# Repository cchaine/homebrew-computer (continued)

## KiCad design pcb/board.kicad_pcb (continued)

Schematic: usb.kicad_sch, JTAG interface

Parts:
C28, C29, C30, C33, C37, C39, C40, C41, C42, C43, C44, C45, C46, C48: 0.1u; C_0402_1005Metric
C31: 10n; C_0402_1005Metric
C32, C36, C38: 4.7u; CP_Elec_4x4.5
C34: 3.3uF; C_1210_3225Metric
C35: 100pF; C_0402_1005Metric
C49, C50: 16p; C_0402_1005Metric
D1, D2: D_TVS; DO-214AC
FB1, FB2, FB3: 600R/0.5A; L_0603_1608Metric
J1: Conn_02x03_Counter_Clockwise; IDC-Header_2x03_P2.54mm_Horizontal
J2: USB_B; BEL_SS-52300-001
R7, R8, R9, R10, R14, R15, R16: 10k; R_0402_1005Metric
R11: 22; R_0402_1005Metric
R12: 68; R_0402_1005Metric
R13: 1k; R_0402_1005Metric
R17: 2.2k; R_0402_1005Metric
R18: 12k/1%; R_0402_1005Metric
U6: 74LVC1G04; SOT-23-5
U7: SN74AVC4T245PW; TSSOP-16_4.4x5mm_P0.65mm
U8: FT2232HQ; QFN-64-1EP_9x9mm_P0.5mm_EP4.35x4.35mm
U9: 93LCxxBxxOT; SOT-23-6
Y1: 12MHz; Crystal_SMD_EuroQuartz_MT-4Pin_3.2x2.5mm

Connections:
/USB interface/D+: D2.2 (A2), J2.3 (D+), U8.8 (DP)
/USB interface/D-: D1.2 (A2), J2.2 (D-), U8.7 (DM)
/USB interface/VBUS: FB1.1, R7.1, U6.2
/USB interface/VPHY: C36.1, C37.1, FB2.1, U8.4 (VPHY)
/USB interface/VPLL: C38.1, C39.1, FB3.1, U8.9 (VPLL)
GND: C28.2, C29.2, C30.2, C31.2, C32.2, C33.2, C34.2, C35.2, C36.2, C37.2, C38.2, C39.2, C40.2, C41.2, C42.2, C43.2, C44.2, C45.2, C46.2, C48.2, C49.2, C50.2, D1.1 (A1), D2.1 (A1), J1.4, J2.4 (GND), R7.2, R18.2, U6.3 (GND), U7.8 (GND), U7.9 (GND), U8.1 (GND), U8.5 (GND), U8.10 (AGND), U8.11 (GND), U8.13 (TEST), U8.15 (GND), U8.25 (GND), U8.35 (GND), U8.47 (GND), U8.51 (GND), U8.65 (GND), U9.2 (GND), Y1.2, Y1.4; also elsewhere on the board
unnamed: C31.1, FB1.2, J2.1 (VBUS)
unnamed: C35.1, R12.2
unnamed: C49.1, U8.2 (OSCI), Y1.1
unnamed: C50.1, U8.3 (OSCO), Y1.3
unnamed: R9.2, R11.2, U7.11 (2B1)
unnamed: R13.1, U8.14 (~RESET)
unnamed: R14.2, R17.2, U9.1 (DO)
unnamed: R15.2, U8.62 (EECLK), U9.4 (CLK)
unnamed: R16.2, U8.63 (EECS), U9.5 (CS)
unnamed: R17.1, U8.61 (EEDATA), U9.3 (DI)
unnamed: R18.1, U8.6 (REF)
unnamed: U6.4, U7.14 (2~OE), U7.15 (1~OE)
unnamed: U7.4 (1A1), U8.16 (ADBUS0)
unnamed: U7.5 (1A2), U8.17 (ADBUS1)
unnamed: U7.6 (2A1), U8.18 (ADBUS2)
unnamed: U7.7 (2A2), U8.19 (ADBUS3)
SPI_PROGRAM#: U8.52 (BCBUS1); also elsewhere on the board
TCK: J1.2, R12.1, U7.13 (1B1); also elsewhere on the board
TDI: J1.3, R8.2, U7.12 (1B2); also elsewhere on the board
TDO: J1.6, R11.1; also elsewhere on the board
TMS: J1.5, R10.2, U7.10 (2B2); also elsewhere on the board
USB_SPI_CLK: U8.38 (BDBUS0); also elsewhere on the board
USB_SPI_CONFIG_CS: U8.41 (BDBUS3); also elsewhere on the board
USB_SPI_MISO: U8.40 (BDBUS2); also elsewhere on the board
USB_SPI_MOSI: U8.39 (BDBUS1); also elsewhere on the board
USB_SPI_ROM_CS: U8.43 (BDBUS4); also elsewhere on the board
VCCAUX: C28.1, C29.1, C30.1, C32.1, C33.1, C34.1, C40.1, C41.1, C42.1, C43.1, C44.1, C45.1, C46.1, C48.1, FB2.2, FB3.2, J1.1, R8.1, R9.1, R10.1, R13.2, R14.1, R15.1, R16.1, U6.5 (VCC), U7.1 (VCCA), U7.2 (1DIR), U7.3 (2DIR), U7.16 (VCCB), U8.12 (VCORE), U8.20 (VCCIO), U8.31 (VCCIO), U8.37 (VCORE), U8.42 (VCCIO), U8.49 (VREGOUT), U8.50 (VREGIN), U8.56 (VCCIO), U8.64 (VCORE), U9.6 (VCC); also elsewhere on the board

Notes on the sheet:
BCBUS1 is TriS-PU by default

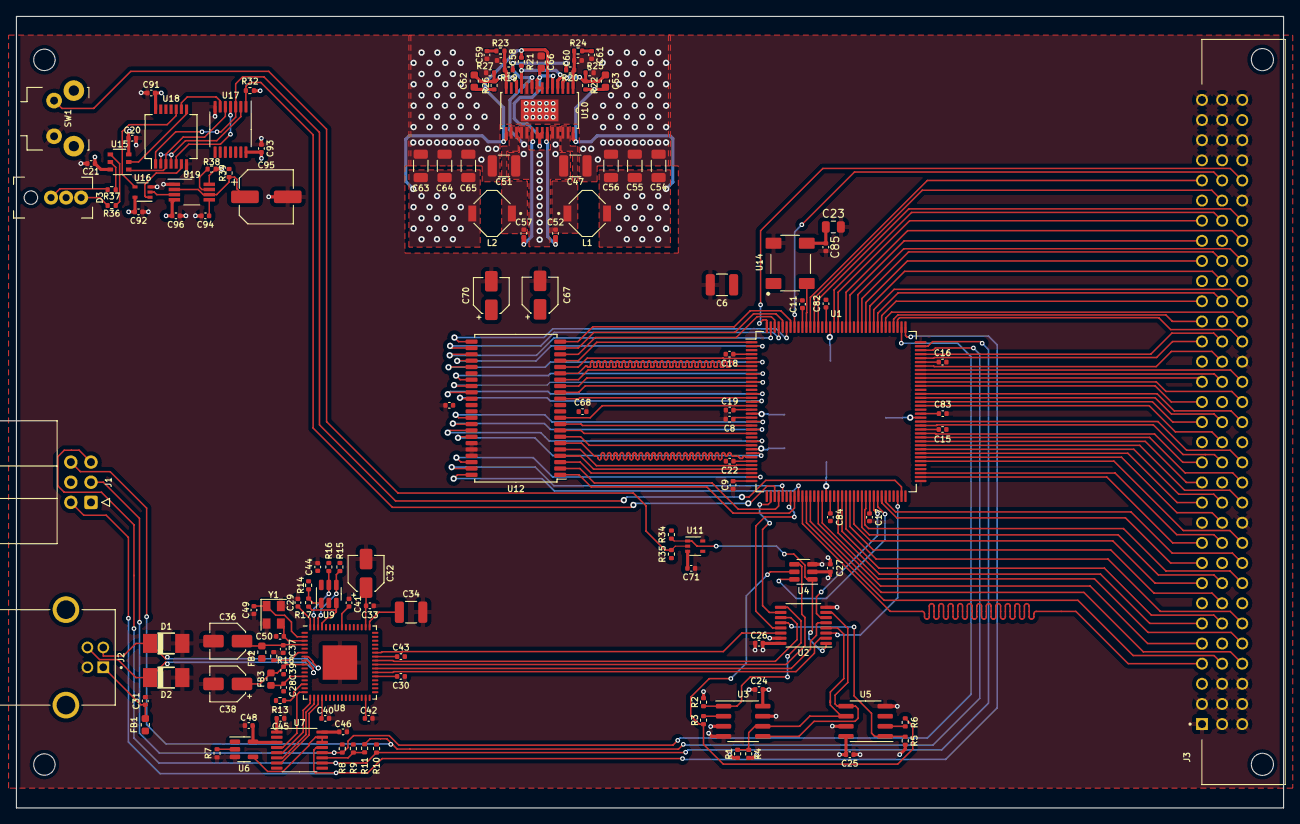
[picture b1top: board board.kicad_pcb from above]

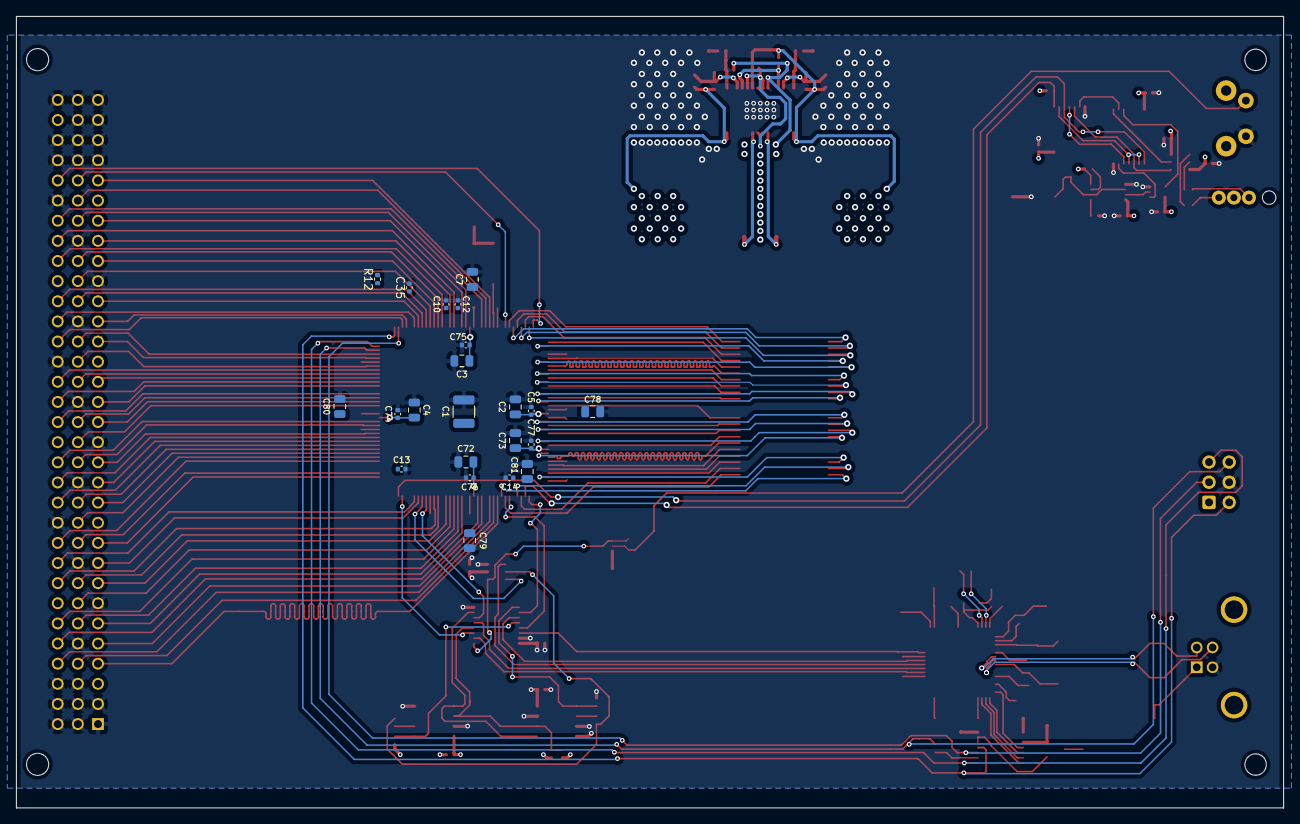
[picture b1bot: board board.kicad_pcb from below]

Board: 4 copper layers, 159.9 x 99.9 mm, 158 parts (22 on the bottom side), 172 nets.

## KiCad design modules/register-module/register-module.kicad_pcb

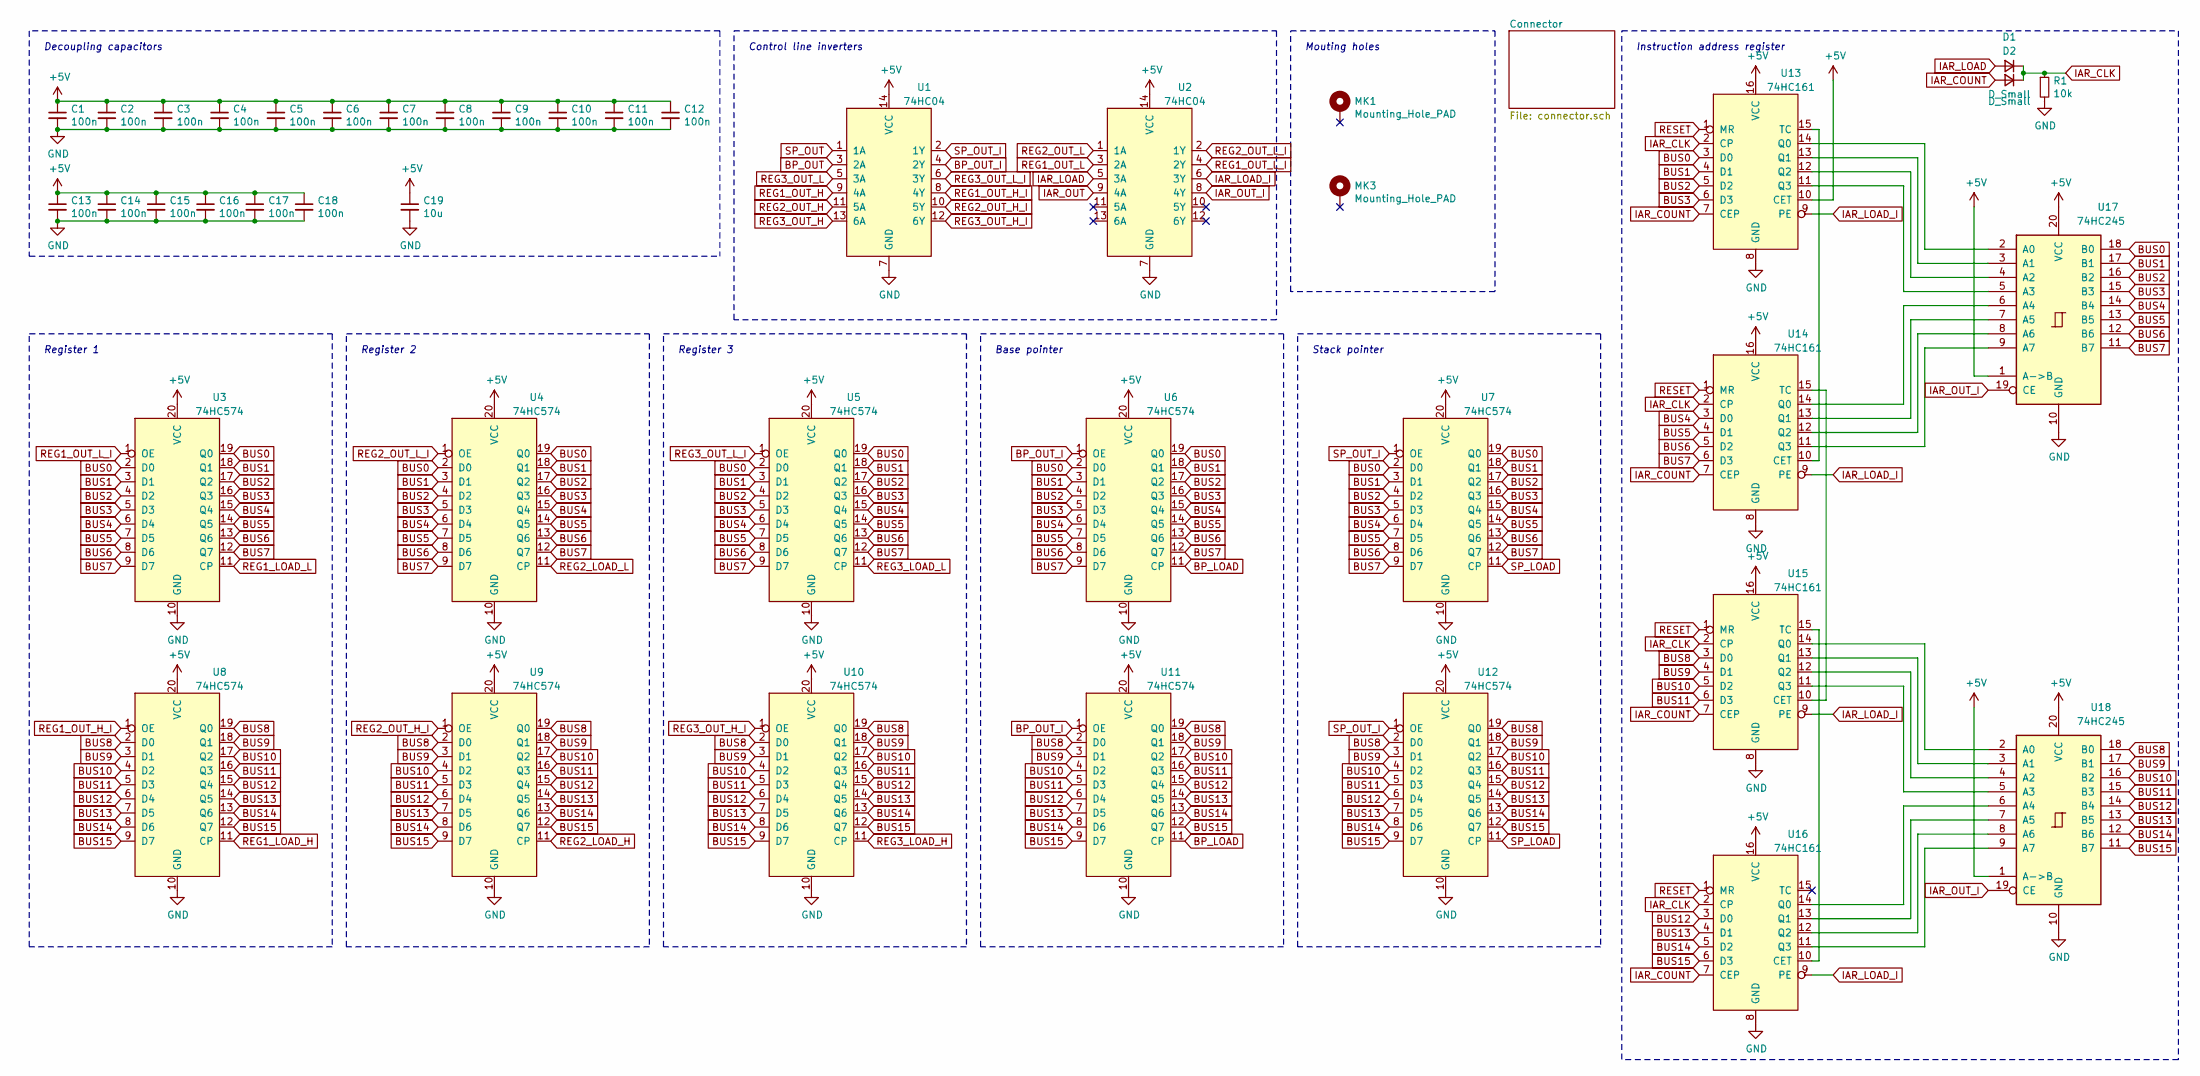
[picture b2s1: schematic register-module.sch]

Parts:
C1, C2, C3, C4, C5, C6, C7, C8, C9, C10, C11, C12, C13, C14, C15, C16, C17, C18: 100n; C_0805_2012Metric
C19: 10u; C_1812_4532Metric
D1, D2: D_Small; D_SOD-523
MK1, MK3: Mounting_Hole_PAD; MountingHole_2.7mm
R1: 10k; R_0805_2012Metric
U1, U2: 74HC04; DIP-14_W7.62mm
U3, U4, U5, U6, U7, U8, U9, U10, U11, U12: 74HC574; DIP-20_W7.62mm
U13, U14, U15, U16: 74HC161; SOIC-16_3.9x9.9mm_P1.27mm
U17, U18: 74HC245; DIP-20_W7.62mm

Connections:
+5V: C1.1, C2.1, C3.1, C4.1, C5.1, C6.1, C7.1, C8.1, C9.1, C10.1, C11.1, C12.1, C13.1, C14.1, C15.1, C16.1, C17.1, C18.1, C19.1, U1.14 (VCC), U2.14 (VCC), U3.20 (VCC), U4.20 (VCC), U5.20 (VCC), U6.20 (VCC), U7.20 (VCC), U8.20 (VCC), U9.20 (VCC), U10.20 (VCC), U11.20 (VCC), U12.20 (VCC), U13.10 (CET), U13.16 (VCC), U14.16 (VCC), U15.16 (VCC), U16.16 (VCC), U17.1 (A->B), U17.20 (VCC), U18.1 (A->B), U18.20 (VCC); also elsewhere on the board
BP_LOAD: U6.11 (CP), U11.11 (CP); also elsewhere on the board
BP_OUT: U1.3 (2A); also elsewhere on the board
BP_OUT_I: U1.4 (2Y), U6.1 (OE), U11.1 (OE)
BUS0: U3.2 (D0), U3.19 (Q0), U4.2 (D0), U4.19 (Q0), U5.2 (D0), U5.19 (Q0), U6.2 (D0), U6.19 (Q0), U7.2 (D0), U7.19 (Q0), U13.3 (D0), U17.18 (B0); also elsewhere on the board
BUS1: U3.3 (D1), U3.18 (Q1), U4.3 (D1), U4.18 (Q1), U5.3 (D1), U5.18 (Q1), U6.3 (D1), U6.18 (Q1), U7.3 (D1), U7.18 (Q1), U13.4 (D1), U17.17 (B1); also elsewhere on the board
BUS2: U3.4 (D2), U3.17 (Q2), U4.4 (D2), U4.17 (Q2), U5.4 (D2), U5.17 (Q2), U6.4 (D2), U6.17 (Q2), U7.4 (D2), U7.17 (Q2), U13.5 (D2), U17.16 (B2); also elsewhere on the board
BUS3: U3.5 (D3), U3.16 (Q3), U4.5 (D3), U4.16 (Q3), U5.5 (D3), U5.16 (Q3), U6.5 (D3), U6.16 (Q3), U7.5 (D3), U7.16 (Q3), U13.6 (D3), U17.15 (B3); also elsewhere on the board
BUS4: U3.6 (D4), U3.15 (Q4), U4.6 (D4), U4.15 (Q4), U5.6 (D4), U5.15 (Q4), U6.6 (D4), U6.15 (Q4), U7.6 (D4), U7.15 (Q4), U14.3 (D0), U17.14 (B4); also elsewhere on the board
BUS5: U3.7 (D5), U3.14 (Q5), U4.7 (D5), U4.14 (Q5), U5.7 (D5), U5.14 (Q5), U6.7 (D5), U6.14 (Q5), U7.7 (D5), U7.14 (Q5), U14.4 (D1), U17.13 (B5); also elsewhere on the board
BUS6: U3.8 (D6), U3.13 (Q6), U4.8 (D6), U4.13 (Q6), U5.8 (D6), U5.13 (Q6), U6.8 (D6), U6.13 (Q6), U7.8 (D6), U7.13 (Q6), U14.5 (D2), U17.12 (B6); also elsewhere on the board
BUS7: U3.9 (D7), U3.12 (Q7), U4.9 (D7), U4.12 (Q7), U5.9 (D7), U5.12 (Q7), U6.9 (D7), U6.12 (Q7), U7.9 (D7), U7.12 (Q7), U14.6 (D3), U17.11 (B7); also elsewhere on the board
BUS8: U8.2 (D0), U8.19 (Q0), U9.2 (D0), U9.19 (Q0), U10.2 (D0), U10.19 (Q0), U11.2 (D0), U11.19 (Q0), U12.2 (D0), U12.19 (Q0), U15.3 (D0), U18.18 (B0); also elsewhere on the board
BUS9: U8.3 (D1), U8.18 (Q1), U9.3 (D1), U9.18 (Q1), U10.3 (D1), U10.18 (Q1), U11.3 (D1), U11.18 (Q1), U12.3 (D1), U12.18 (Q1), U15.4 (D1), U18.17 (B1); also elsewhere on the board
BUS10: U8.4 (D2), U8.17 (Q2), U9.4 (D2), U9.17 (Q2), U10.4 (D2), U10.17 (Q2), U11.4 (D2), U11.17 (Q2), U12.4 (D2), U12.17 (Q2), U15.5 (D2), U18.16 (B2); also elsewhere on the board
BUS11: U8.5 (D3), U8.16 (Q3), U9.5 (D3), U9.16 (Q3), U10.5 (D3), U10.16 (Q3), U11.5 (D3), U11.16 (Q3), U12.5 (D3), U12.16 (Q3), U15.6 (D3), U18.15 (B3); also elsewhere on the board
BUS12: U8.6 (D4), U8.15 (Q4), U9.6 (D4), U9.15 (Q4), U10.6 (D4), U10.15 (Q4), U11.6 (D4), U11.15 (Q4), U12.6 (D4), U12.15 (Q4), U16.3 (D0), U18.14 (B4); also elsewhere on the board
BUS13: U8.7 (D5), U8.14 (Q5), U9.7 (D5), U9.14 (Q5), U10.7 (D5), U10.14 (Q5), U11.7 (D5), U11.14 (Q5), U12.7 (D5), U12.14 (Q5), U16.4 (D1), U18.13 (B5); also elsewhere on the board
BUS14: U8.8 (D6), U8.13 (Q6), U9.8 (D6), U9.13 (Q6), U10.8 (D6), U10.13 (Q6), U11.8 (D6), U11.13 (Q6), U12.8 (D6), U12.13 (Q6), U16.5 (D2), U18.12 (B6); also elsewhere on the board
BUS15: U8.9 (D7), U8.12 (Q7), U9.9 (D7), U9.12 (Q7), U10.9 (D7), U10.12 (Q7), U11.9 (D7), U11.12 (Q7), U12.9 (D7), U12.12 (Q7), U16.6 (D3), U18.11 (B7); also elsewhere on the board
GND: C1.2, C2.2, C3.2, C4.2, C5.2, C6.2, C7.2, C8.2, C9.2, C10.2, C11.2, C12.2, C13.2, C14.2, C15.2, C16.2, C17.2, C18.2, C19.2, R1.2, U1.7 (GND), U2.7 (GND), U3.10 (GND), U4.10 (GND), U5.10 (GND), U6.10 (GND), U7.10 (GND), U8.10 (GND), U9.10 (GND), U10.10 (GND), U11.10 (GND), U12.10 (GND), U13.8 (GND), U14.8 (GND), U15.8 (GND), U16.8 (GND), U17.10 (GND), U18.10 (GND); also elsewhere on the board
IAR_CLK: D1.1 (K), D2.1 (K), R1.1, U13.2 (CP), U14.2 (CP), U15.2 (CP), U16.2 (CP); also elsewhere on the board
IAR_COUNT: D2.2 (A), U13.7 (CEP), U14.7 (CEP), U15.7 (CEP), U16.7 (CEP); also elsewhere on the board
IAR_LOAD: D1.2 (A), U2.5 (3A); also elsewhere on the board
IAR_LOAD_I: U2.6 (3Y), U13.9 (PE), U14.9 (PE), U15.9 (PE), U16.9 (PE)
IAR_OUT: U2.9 (4A); also elsewhere on the board
IAR_OUT_I: U2.8 (4Y), U17.19 (CE), U18.19 (CE)
unnamed: U13.11 (Q3), U17.5 (A3)
unnamed: U13.12 (Q2), U17.4 (A2)
unnamed: U13.13 (Q1), U17.3 (A1)
unnamed: U13.14 (Q0), U17.2 (A0)
unnamed: U13.15 (TC), U14.10 (CET)
unnamed: U14.11 (Q3), U17.9 (A7)
unnamed: U14.12 (Q2), U17.8 (A6)
unnamed: U14.13 (Q1), U17.7 (A5)
unnamed: U14.14 (Q0), U17.6 (A4)
unnamed: U14.15 (TC), U15.10 (CET)
unnamed: U15.11 (Q3), U18.5 (A3)
unnamed: U15.12 (Q2), U18.4 (A2)
unnamed: U15.13 (Q1), U18.3 (A1)
unnamed: U15.14 (Q0), U18.2 (A0)
unnamed: U15.15 (TC), U16.10 (CET)
unnamed: U16.11 (Q3), U18.9 (A7)
unnamed: U16.12 (Q2), U18.8 (A6)
unnamed: U16.13 (Q1), U18.7 (A5)
unnamed: U16.14 (Q0), U18.6 (A4)
REG1_LOAD_H: U8.11 (CP); also elsewhere on the board
REG1_LOAD_L: U3.11 (CP); also elsewhere on the board
REG1_OUT_H: U1.9 (4A); also elsewhere on the board
REG1_OUT_H_I: U1.8 (4Y), U8.1 (OE)
REG1_OUT_L: U2.3 (2A); also elsewhere on the board
REG1_OUT_L_I: U2.4 (2Y), U3.1 (OE)
REG2_LOAD_H: U9.11 (CP); also elsewhere on the board
REG2_LOAD_L: U4.11 (CP); also elsewhere on the board
REG2_OUT_H: U1.11 (5A); also elsewhere on the board
REG2_OUT_H_I: U1.10 (5Y), U9.1 (OE)
REG2_OUT_L: U2.1 (1A); also elsewhere on the board
REG2_OUT_L_I: U2.2 (1Y), U4.1 (OE)
REG3_LOAD_H: U10.11 (CP); also elsewhere on the board
REG3_LOAD_L: U5.11 (CP); also elsewhere on the board
REG3_OUT_H: U1.13 (6A); also elsewhere on the board
REG3_OUT_H_I: U1.12 (6Y), U10.1 (OE)
REG3_OUT_L: U1.5 (3A); also elsewhere on the board
REG3_OUT_L_I: U1.6 (3Y), U5.1 (OE)
RESET: U13.1 (MR), U14.1 (MR), U15.1 (MR), U16.1 (MR); also elsewhere on the board
SP_LOAD: U7.11 (CP), U12.11 (CP); also elsewhere on the board
SP_OUT: U1.1 (1A); also elsewhere on the board
SP_OUT_I: U1.2 (1Y), U7.1 (OE), U12.1 (OE)

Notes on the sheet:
Register 1
Register 2
Register 3
Base pointer
Stack pointer
Control line inverters
Decoupling capacitors
Mouting holes
Instruction address register

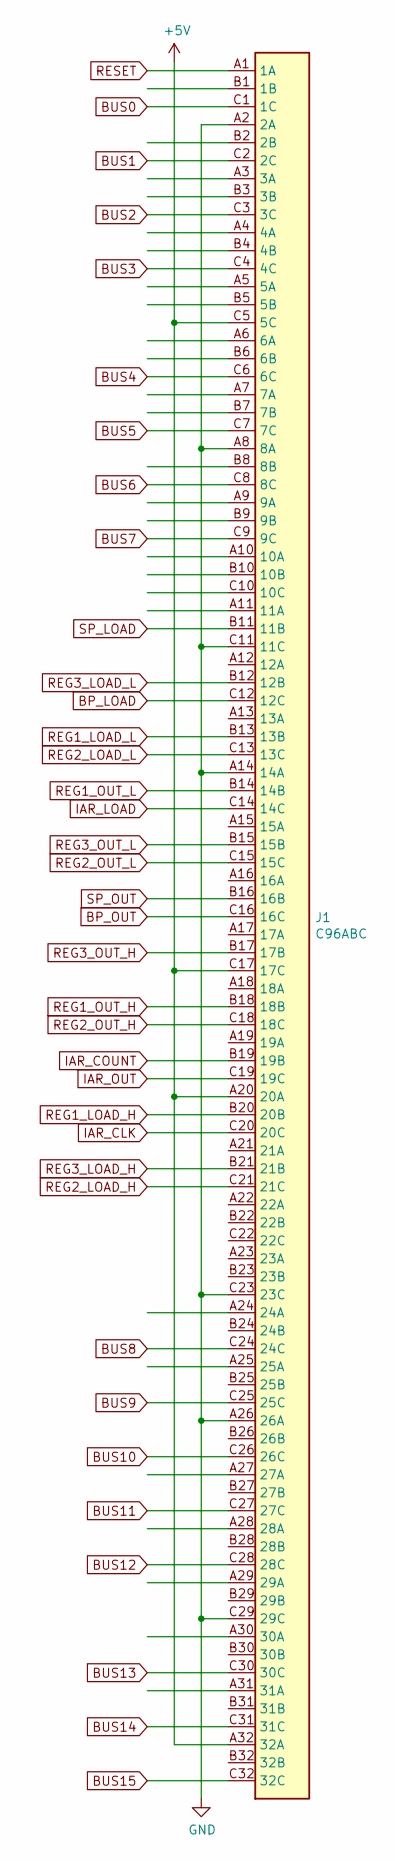
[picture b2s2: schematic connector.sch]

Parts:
J1: C96ABC; DIN41612_C_3x32_Male_Horizontal_THT_ABC

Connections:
+5V: J1.A20 (20A), J1.A32 (32A), J1.C5 (5C), J1.C17 (17C); also elsewhere on the board
BP_LOAD: J1.C12 (12C); also elsewhere on the board
BP_OUT: J1.C16 (16C); also elsewhere on the board
BUS0: J1.C1 (1C); also elsewhere on the board
BUS1: J1.C2 (2C); also elsewhere on the board
BUS2: J1.C3 (3C); also elsewhere on the board
BUS3: J1.C4 (4C); also elsewhere on the board
BUS4: J1.C6 (6C); also elsewhere on the board
BUS5: J1.C7 (7C); also elsewhere on the board
BUS6: J1.C8 (8C); also elsewhere on the board
BUS7: J1.C9 (9C); also elsewhere on the board
BUS8: J1.C24 (24C); also elsewhere on the board
BUS9: J1.C25 (25C); also elsewhere on the board
BUS10: J1.C26 (26C); also elsewhere on the board
BUS11: J1.C27 (27C); also elsewhere on the board
BUS12: J1.C28 (28C); also elsewhere on the board
BUS13: J1.C30 (30C); also elsewhere on the board
BUS14: J1.C31 (31C); also elsewhere on the board
BUS15: J1.C32 (32C); also elsewhere on the board
GND: J1.A2 (2A), J1.A8 (8A), J1.A14 (14A), J1.A26 (26A), J1.C11 (11C), J1.C23 (23C), J1.C29 (29C); also elsewhere on the board
IAR_CLK: J1.C20 (20C); also elsewhere on the board
IAR_COUNT: J1.B19 (19B); also elsewhere on the board
IAR_LOAD: J1.C14 (14C); also elsewhere on the board
IAR_OUT: J1.C19 (19C); also elsewhere on the board
REG1_LOAD_H: J1.B20 (20B); also elsewhere on the board
REG1_LOAD_L: J1.B13 (13B); also elsewhere on the board
REG1_OUT_H: J1.B18 (18B); also elsewhere on the board
REG1_OUT_L: J1.B14 (14B); also elsewhere on the board
REG2_LOAD_H: J1.C21 (21C); also elsewhere on the board
REG2_LOAD_L: J1.C13 (13C); also elsewhere on the board
REG2_OUT_H: J1.C18 (18C); also elsewhere on the board
REG2_OUT_L: J1.C15 (15C); also elsewhere on the board
REG3_LOAD_H: J1.B21 (21B); also elsewhere on the board
REG3_LOAD_L: J1.B12 (12B); also elsewhere on the board
REG3_OUT_H: J1.B17 (17B); also elsewhere on the board
REG3_OUT_L: J1.B15 (15B); also elsewhere on the board
RESET: J1.A1 (1A); also elsewhere on the board
SP_LOAD: J1.B11 (11B); also elsewhere on the board
SP_OUT: J1.B16 (16B); also elsewhere on the board

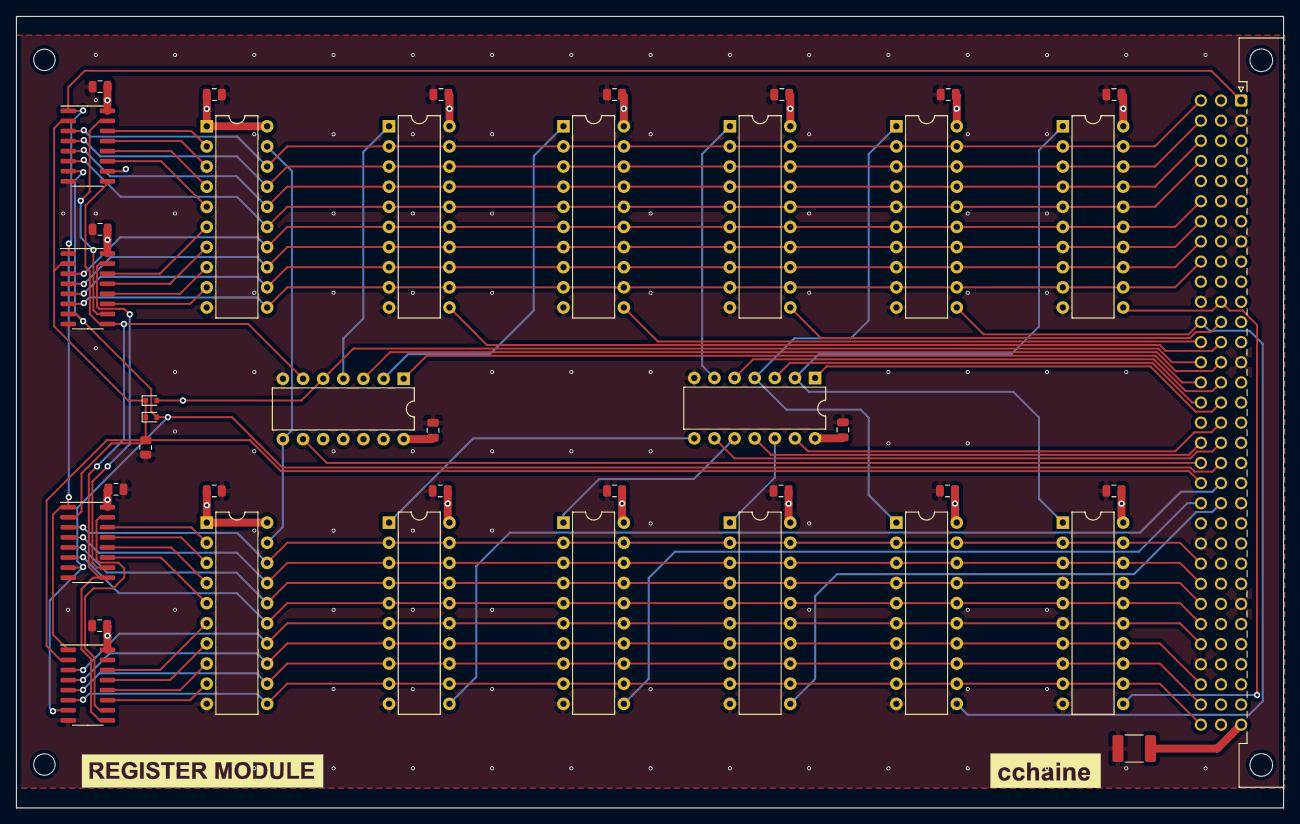
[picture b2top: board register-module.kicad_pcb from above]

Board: 4 copper layers, 159.9 x 99.9 mm, 43 parts (0 on the bottom side), 68 nets.

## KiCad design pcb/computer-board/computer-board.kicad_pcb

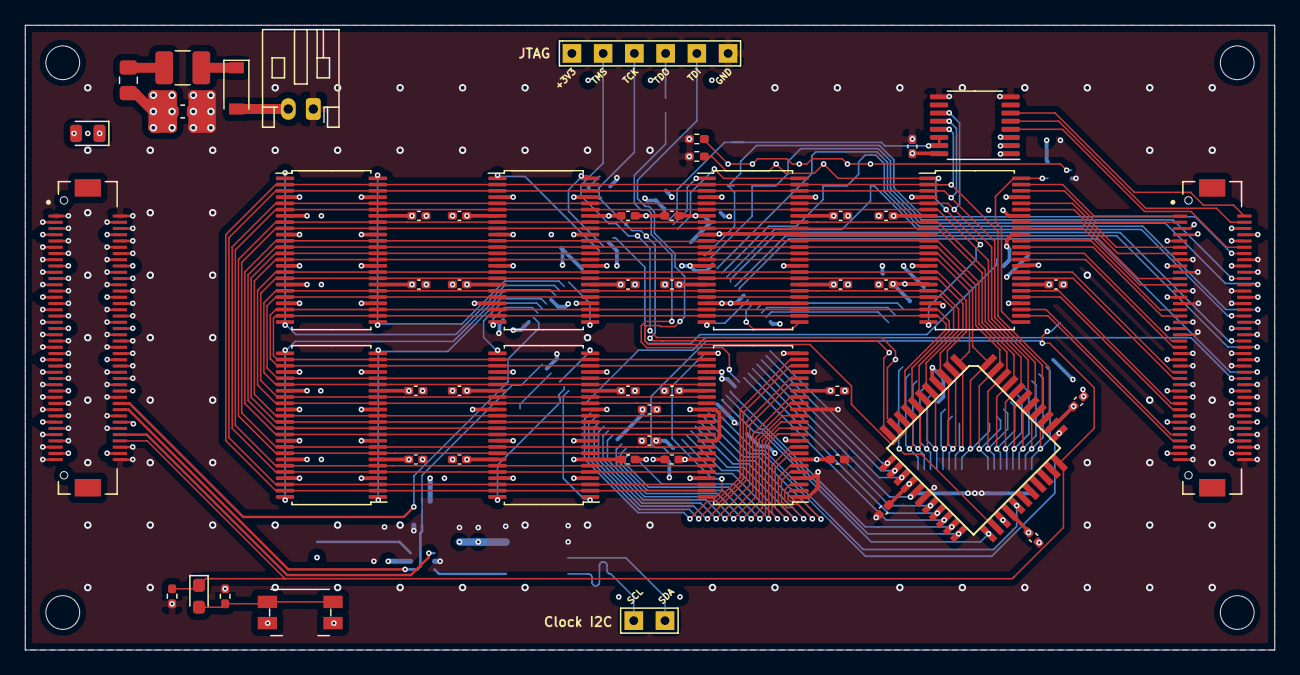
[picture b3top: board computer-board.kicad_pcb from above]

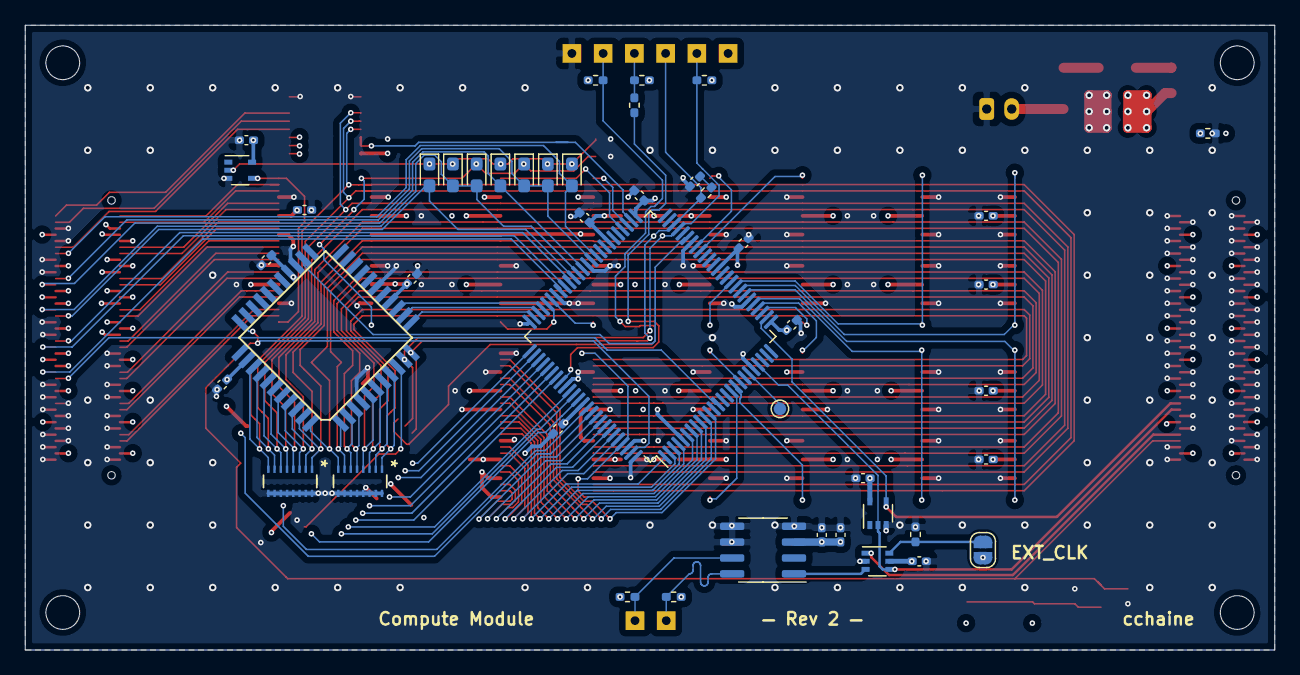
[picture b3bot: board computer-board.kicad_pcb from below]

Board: 4 copper layers, 100.0 x 50.0 mm, 109 parts (45 on the bottom side), 120 nets.

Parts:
C1: 10u; C_0603_1608Metric_Pad1.08x0.95mm_HandSolder
C3: 100p; C_0402_1005Metric_Pad0.74x0.62mm_HandSolder
C4, C5, C6, C7, C8, C9, C10, C11, C12, C13, C14, C15, C16, C17, C18, C19, C20, C21, C22, C23, C24, C25, C26, C27, C28, C29, C30, C31, C32, C33, C34, C35, C36, C37, C38, C39, C40, C41, C42, C43, C44, C45, C46, C48, C49, C50: 100n; C_0402_1005Metric_Pad0.74x0.62mm_HandSolder
C47: 10n; C_0402_1005Metric_Pad0.74x0.62mm_HandSolder
D1: Schottky 2A; D_SOD-123
D2, D3, D4, D5, D6, D7, D8, D9: D_Small; D_0603_1608Metric_Pad1.05x0.95mm_HandSolder
D10: LED_Small; LED_0805_2012Metric
F1: A déterminer; Fuse_1210_3225Metric_Pad1.42x2.65mm_HandSolder
FB1: 100 @ 100MHz; L_0805_2012Metric_Pad1.15x1.40mm_HandSolder
H1, H2, H3, H4: M3; MountingHole_2.7mm_M2.5
J1: Conn_01x02_Male; JST_PH_S2B-PH-K_1x02_P2.00mm_Horizontal
J2, J7: Conn_02x40_Odd_Even; HRS_DF17(2.0)-80DP-0.5V(57)
JP1: Jumper_NC_Small; SolderJumper-2_P1.3mm_Open_RoundedPad1.0x1.5mm
R1, R2, R3, R4, R7, R9, R10, R11, R12, R13: 10k; R_0402_1005Metric_Pad0.72x0.64mm_HandSolder
R5: 22; R_0402_1005Metric_Pad0.72x0.64mm_HandSolder
R6: 68; R_0402_1005Metric_Pad0.72x0.64mm_HandSolder
R8: 470; R_0402_1005Metric_Pad0.72x0.64mm_HandSolder
SW1: SW_Push; Panasonic_EVQPUJ_EVQPUA
TP1: TestPoint_Small; TestPoint_Pad_D1.0mm
TP2, TP3, TP4, TP5, TP6, TP7, TP8, TP10: TestPoint_Small; TestPoint_THTPad_1.5x1.5mm_Drill0.7mm
U2, U3: YC248
U4: XC9572XL-10VQG44C; VQFP-44
U5: SN74AVC16T245DGGR; TSSOP-48_6.1x12.5mm_P0.5mm
U6: SN74AVC4T245PWR; TSSOP-16_4.4x5mm_P0.65mm
U7, U18: 74LVC1G14GW,125; SOT-353_SC-70-5
U8: XC9536XL-10VQG44C; VQFP-44
U9, U10, U11, U12, U13, U15: 74LVC16374ADGG,112; TSSOP-48_6.1x12.5mm_P0.5mm
U14: XC95144XL-10TQ100C; TQFP-100_14x14mm_P0.5mm
U16: DS1077LZ-60+; SOIC-8_3.9x4.9mm_P1.27mm
U17: 74LVC1G157GC-Q100H; SOT-363_SC-70-6

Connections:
+3V3: C1.1, C4.1, C5.1, C6.1, C7.1, C8.1, C9.1, C10.1, C11.1, C12.1, C13.1, C14.1, C15.1, C16.1, C17.1, C18.1, C19.1, C20.1, C21.1, C22.1, C23.1, C24.1, C25.1, C26.1, C27.1, C28.1, C29.1, C30.1, C31.1, C32.1, C33.1, C34.1, C35.1, C36.1, C37.1, C38.1, C39.1, C40.1, C41.1, C42.1, C43.1, C44.1, C45.1, C46.1, C47.1, C48.1, C49.1, C50.1, D10.2, FB1.1, J2.7, J2.8, J2.17, J2.18, J2.27, J2.28, J2.37, J2.38, J2.47, J2.48, J2.57, J2.58, J2.67, J2.68, J2.77, J2.78, J7.7, J7.8, J7.17, J7.18, J7.27, J7.28, J7.37, J7.38, J7.47, J7.48, J7.57, J7.58, J7.67, J7.68, J7.77, J7.78, JP1.2, R2.1, R3.1, R4.1, R9.1, R10.1, SW1.1, TP2.1, U4.15, U4.26, U4.35, U5.7, U5.18, U5.31, U5.42, U6.1, U6.2, U6.3, U6.16, U7.5, U8.15, U8.26, U8.35, U9.7, U9.18, U9.31, U9.42, U10.7, U10.18, U10.31, U10.42, U11.7, U11.18, U11.31, U11.42, U12.7, U12.18, U12.31, U12.42, U13.7, U13.18, U13.31, U13.42, U14.5, U14.26, U14.38, U14.51, U14.57, U14.88, U14.98, U15.7, U15.18, U15.31, U15.42, U16.3, U17.5, U18.5
/ALU_OUT_I: U4.34, U14.90
/ALU_TDI: R2.2, TP3.1, U4.9
/ALU_TDO: U4.24, U8.9
/A_IN: U4.27, U14.89
/BP_IN: U13.25, U13.48, U14.32
/BP_OUT_I: U13.1, U13.24, U14.30
/B_IN: U4.23, U14.87
/CLK: J2.64, U14.22, U17.4, U18.2
/CLK_I: J2.62, U14.27, U18.4
/CTRL_TDI: U8.24, U14.45
/CTRL_TDO: R5.1, U14.83
/Control Logic/INSTR_IN: U14.97, U15.25, U15.48
/Control Logic/IR1: U14.91, U15.2
/Control Logic/IR2: U14.92, U15.3
/Control Logic/IR3: U14.93, U15.5
/Control Logic/IR4: U14.94, U15.6
/Control Logic/IR5: U14.95, U15.8
/Control Logic/IR6: U14.96, U15.9
/Control Logic/IR7: U14.1, U15.11
/Control Logic/IR8: U14.2, U15.12
/Control Logic/IR9: U14.3, U15.13
/Control Logic/IR10: U14.4, U15.14
/Control Logic/IR11: U14.6, U15.16
/Control Logic/IR12: U14.7, U15.17
/Control Logic/IR13: U14.8, U15.19
/Control Logic/IR14: U14.9, U15.20
/Control Logic/IR15: U14.10, U15.22
/Control Logic/IR16: U14.11, U15.23
/EXT_CLK: J2.72, U17.1
/FLAG_CARRY: U4.14, U14.78
/FLAG_NEG: U4.13, U14.77
/FLAG_OVERFLOW: U4.16, U14.79
/FLAG_ZERO: U4.12, U14.76
/INT: J7.42, U14.66
/INT_OUT_I: U6.14, U6.15, U14.52
/IO/INT0: J7.12, U6.4
/IO/INT1: J7.4, U6.5
/IO/INT2: J7.2, U6.6
/IO/IO1: J7.1, U5.47
/IO/IO2: J7.3, U5.46
/IO/IO3: J7.11, U5.44
/IO/IO4: J7.13, U5.43
/IO/IO5: J7.21, U5.41
/IO/IO6: J7.23, U5.40
/IO/IO7: J7.31, U5.38
/IO/IO8: J7.33, U5.37
/IO/IO9: J7.41, U5.36
/IO/IO10: J7.43, U5.35
/IO/IO11: J7.51, U5.33
/IO/IO12: J7.53, U5.32
/IO/IO13: J7.61, U5.30
/IO/IO14: J7.63, U5.29
/IO/IO15: J7.71, U5.27
/IO/IO16: J7.73, U5.26
/IO_ADDR_IN: D9.2, J7.14, U14.60
/IO_IN: D7.2, J7.24, U14.63
/IO_INB: D8.2, J7.34, U14.65
/IO_OUT: D3.2, D4.2, J7.22, U14.61
/IO_OUTB: D5.2, D6.2, J7.32, U14.64
/MEM_READY: J7.54, U14.13
/OP1: U4.22, U14.86
/OP2: U4.21, U14.85
/OP3: U4.20, U14.82
/OP4: U4.19, U14.81
/OP_IN: U4.18, U14.80
/PC_COUNT: U8.13, U14.73
/PC_IN: U8.14, U14.72
/PC_OUT_I: U8.12, U14.74
/PERIPH_MEM_SPACE: J7.52, U14.68
/REG1_IN_H: U9.25, U14.29
/REG1_IN_L: U9.48, U14.17
/REG1_OUT_H_I: U9.24, U14.18
/REG1_OUT_L_I: U9.1, U14.16
/REG2_IN_H: U10.25, U14.35
/REG2_IN_L: U10.48, U14.43
/REG2_OUT_H_I: U10.24, U14.28
/REG2_OUT_L_I: U10.1, U14.42
/REG3_IN_H: U11.25, U14.71
/REG3_IN_L: U11.48, U14.54
/REG3_OUT_H_I: U11.24, U14.70
/REG3_OUT_L_I: U11.1, U14.53
/RESET: D2.1, J2.74, R11.1, U4.33, U8.33, U14.99
/RST_INT: J7.44, U14.67
/SP_IN: U12.25, U12.48, U14.34
/SP_OUT_I: U12.1, U12.24, U14.33
/TCK: R6.1, TP5.1, U4.11, U8.11, U14.48
/TDO_Conn: R3.2, R5.2, TP4.1
/TMS: R4.2, TP6.1, U4.10, U8.10, U14.47
BUS1: U2.8, U4.36, U5.2, U6.13, U8.36, U9.2, U9.47, U10.2, U10.47, U11.2, U11.47, U12.2, U12.47, U13.2, U13.47, U15.47
BUS2: U2.7, U4.37, U5.3, U6.12, U8.37, U9.3, U9.46, U10.3, U10.46, U11.3, U11.46, U12.3, U12.46, U13.3, U13.46, U15.46
BUS3: U2.6, U4.38, U5.5, U6.11, U8.38, U9.5, U9.44, U10.5, U10.44, U11.5, U11.44, U12.5, U12.44, U13.5, U13.44, U15.44
BUS4: U2.5, U4.39, U5.6, U8.39, U9.6, U9.43, U10.6, U10.43, U11.6, U11.43, U12.6, U12.43, U13.6, U13.43, U15.43
BUS5: U2.4, U4.40, U5.8, U8.40, U9.8, U9.41, U10.8, U10.41, U11.8, U11.41, U12.8, U12.41, U13.8, U13.41, U15.41
BUS6: U2.3, U4.41, U5.9, U8.41, U9.9, U9.40, U10.9, U10.40, U11.9, U11.40, U12.9, U12.40, U13.9, U13.40, U15.40
BUS7: U2.2, U4.42, U5.11, U8.42, U9.11, U9.38, U10.11, U10.38, U11.11, U11.38, U12.11, U12.38, U13.11, U13.38, U15.38
BUS8: U2.1, U4.43, U5.12, U8.43, U9.12, U9.37, U10.12, U10.37, U11.12, U11.37, U12.12, U12.37, U13.12, U13.37, U15.37
BUS9: U3.8, U4.44, U5.13, U8.44, U9.13, U9.36, U10.13, U10.36, U11.13, U11.36, U12.13, U12.36, U13.13, U13.36, U15.36
BUS10: U3.7, U4.1, U5.14, U8.1, U9.14, U9.35, U10.14, U10.35, U11.14, U11.35, U12.14, U12.35, U13.14, U13.35, U15.35
BUS11: U3.6, U4.2, U5.16, U8.2, U9.16, U9.33, U10.16, U10.33, U11.16, U11.33, U12.16, U12.33, U13.16, U13.33, U15.33
BUS12: U3.5, U4.3, U5.17, U8.3, U9.17, U9.32, U10.17, U10.32, U11.17, U11.32, U12.17, U12.32, U13.17, U13.32, U15.32
BUS13: U3.4, U4.5, U5.19, U8.5, U9.19, U9.30, U10.19, U10.30, U11.19, U11.30, U12.19, U12.30, U13.19, U13.30, U15.30
BUS14: U3.3, U4.6, U5.20, U8.6, U9.20, U9.29, U10.20, U10.29, U11.20, U11.29, U12.20, U12.29, U13.20, U13.29, U15.29
BUS15: U3.2, U4.7, U5.22, U8.7, U9.22, U9.27, U10.22, U10.27, U11.22, U11.27, U12.22, U12.27, U13.22, U13.27, U15.27
BUS16: U3.1, U4.8, U5.23, U8.8, U9.23, U9.26, U10.23, U10.26, U11.23, U11.26, U12.23, U12.26, U13.23, U13.26, U15.26
EXT_CLK_SELECT: JP1.1, R7.1, U17.6
GND: C1.2, C3.2, C4.2, C5.2, C6.2, C7.2, C8.2, C9.2, C10.2, C11.2, C12.2, C13.2, C14.2, C15.2, C16.2, C17.2, C18.2, C19.2, C20.2, C21.2, C22.2, C23.2, C24.2, C25.2, C26.2, C27.2, C28.2, C29.2, C30.2, C31.2, C32.2, C33.2, C34.2, C35.2, C36.2, C37.2, C38.2, C39.2, C40.2, C41.2, C42.2, C43.2, C44.2, C45.2, C46.2, C47.2, C48.2, C49.2, C50.2, J1.1, J2.1, J2.2, J2.3, J2.4, J2.5, J2.6, J2.9, J2.10, J2.11, J2.12, J2.13, J2.14, J2.15, J2.16, J2.19, J2.20, J2.21, J2.22, J2.23, J2.24, J2.25, J2.26, J2.29, J2.30, J2.31, J2.32, J2.33, J2.34, J2.35, J2.36, J2.39, J2.40, J2.41, J2.42, J2.43, J2.44, J2.45, J2.46, J2.49, J2.50, J2.51, J2.52, J2.53, J2.54, J2.55, J2.56, J2.59, J2.60, J2.61, J2.63, J2.65, J2.66, J2.69, J2.70, J2.71, J2.73, J2.75, J2.76, J2.79, J2.80, J7.5, J7.6, J7.9, J7.10, J7.15, J7.16, J7.19, J7.20, J7.25, J7.26, J7.29, J7.30, J7.35, J7.36, J7.39, J7.40, J7.45, J7.46, J7.49, J7.50, J7.55, J7.56, J7.59, J7.60, J7.62, J7.64, J7.65, J7.66, J7.69, J7.70, J7.72, J7.74, J7.75, J7.76, J7.79, J7.80, R1.2, R7.2, R8.2, R11.2, R12.2, R13.2, TP7.1, U2.9, U2.10, U2.11, U2.12, U2.13, U2.14, U2.15, U2.16, U3.9, U3.10, U3.11, U3.12, U3.13, U3.14, U3.15, U3.16, U4.4, U4.17, U4.25, U5.4, U5.10, U5.15, U5.21, U5.28, U5.34, U5.39, U5.45, U6.8, U6.9, U7.3, U8.4, U8.17, U8.25, U9.4, U9.10, U9.15, U9.21, U9.28, U9.34, U9.39, U9.45, U10.4, U10.10, U10.15, U10.21, U10.28, U10.34, U10.39, U10.45, U11.4, U11.10, U11.15, U11.21, U11.28, U11.34, U11.39, U11.45, U12.4, U12.10, U12.15, U12.21, U12.28, U12.34, U12.39, U12.45, U13.4, U13.10, U13.15, U13.21, U13.28, U13.34, U13.39, U13.45, U14.21, U14.31, U14.44, U14.62, U14.69, U14.75, U14.84, U14.100, U15.1, U15.4, U15.10, U15.15, U15.21, U15.24, U15.28, U15.34, U15.39, U15.45, U16.4, U16.5, U16.6, U17.2, U18.3
INT_CLK: U16.1, U17.3
unnamed: C3.1, R6.2
unnamed: D1.1, F1.2
unnamed: D2.2, R1.1, SW1.2
unnamed: D3.1, D5.1, D7.1, D8.1, D9.1, R13.1, U7.2
unnamed: D4.1, D6.1, R12.1, U5.1, U5.24
unnamed: D10.1, R8.1
unnamed: F1.1, FB1.2
unnamed: TP1.1, U14.20
unnamed: U5.25, U5.48, U7.4
SCL: R9.2, TP8.1, U16.8
SDA: R10.2, TP10.1, U16.7
VCC: D1.2, J1.2
